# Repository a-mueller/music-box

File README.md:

# Music Box

A rfid based player I made. It basically scans for RFID takes, and looks for a WAV file on the SD card with that ID, if found it plays it.
The WAV files need to be 22khz, 16bit mono. Audacity is a good tool to convert mp3s.

## Board

The board is simply a pico with and SD card and the I2S chip.

See KiCad files.

### Schematic

### PCB

### BOM

<table>
<tr><td>CR1</td><td>PMEG2005AEA</td><td>https://uk.farnell.com/nexperia/pmeg2005aea-115/diode-schottky-sod-323/dp/8737843?st=pmeg2005aea</td></tr>
<tr><td>J2</td><td>GCT MEM2061-01-188-00-A</td><td>https://uk.farnell.com/gct-global-connector-technology/mem2061-01-188-00-a/micro-sd-conn-push-push-8pos-smt/dp/2678544?ost=mem2061-01-188-00-a</td></tr>
<tr><td>C6, C2</td><td>0.1uf, 0603</td><td></td></tr>
<tr><td>C5, C1</td><td>10uf, 0805</td><td></td></tr>
<tr><td>R2</td><td>Array, 4x 47k (EXB-N8V473JX)</td><td>https://uk.farnell.com/panasonic/exbn8v473jx/resistor-ccav-array-0402x4-47k/dp/2060146?st=EXBN8V473JX</td></tr>
<tr><td>R6</td><td>649k, 0402</td><td></td></tr>
<tr><td>U1</td><td>I2S Amp, MAX98357AETE+T</td><td>https://uk.farnell.com/analog-devices/max98357aete-t/audio-power-amp-d-40-to-85deg/dp/2949165?st=MAX98357AETE%20T</td></tr>
<tr><td>FB1, FB2</td><td>Ferrite Beads, MMZ1608B121CTDH5</td><td>https://uk.farnell.com/tdk/mmz1608b121ctdh5/ferrite-chip-bead-1608-0-15-ohm/dp/3386884?st=mmz1608b121ctdh5</td></tr>
<tr><td>C4,C3</td><td>220pf, 0402</td><td></td></tr>
<tr><td>J1</td><td>JST, XH 2.5mm</td><td></td></tr>
<tr><td>J4, J3, J5</td><td>JST, PH, 2mm</td><td></td></tr>

</table>

## Software

Flash circuit python (originally I used v9) and copy the lib folder and `code.py` files over. That should be it.

## Case

See FreeCad files in `3dPrinting`, you will need a usbc power board as well to power it (see https://github.com/a-mueller/usbc_power_supply_2)

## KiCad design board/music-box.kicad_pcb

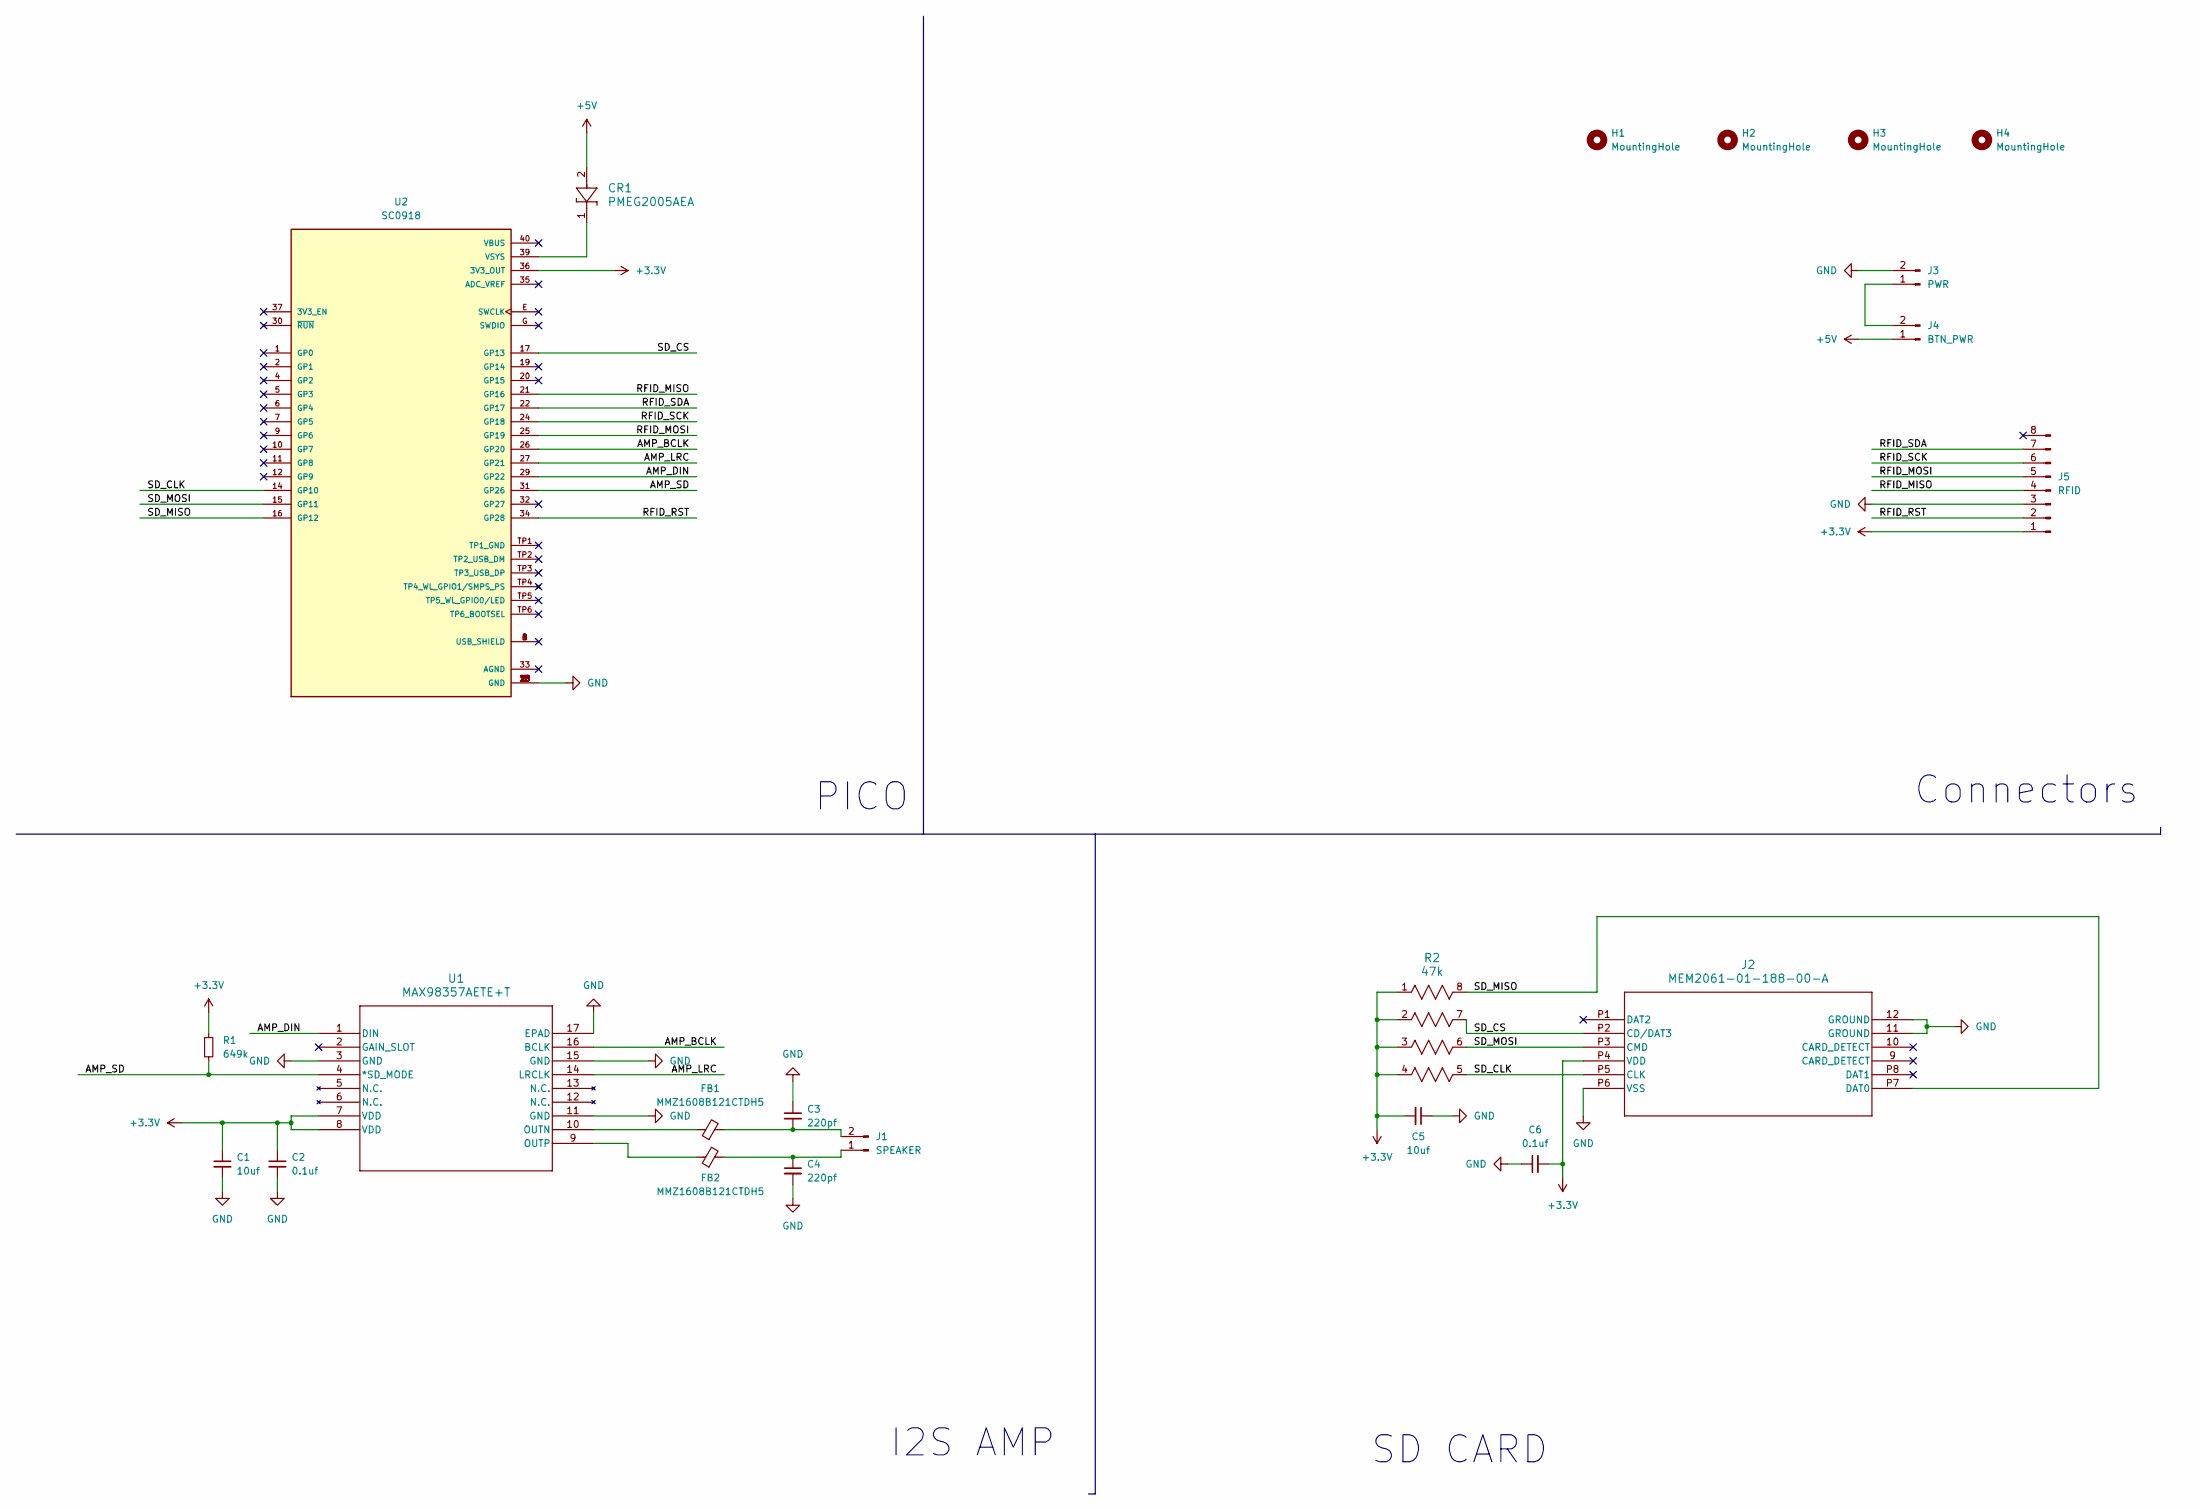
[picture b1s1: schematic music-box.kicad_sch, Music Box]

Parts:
C1, C5: 10uf; C_0805_2012Metric
C2, C6: 0.1uf; C_0603_1608Metric
C3, C4: 220pf; C_0402_1005Metric
CR1: PMEG2005AEA; SOD323F_NEX
FB1, FB2: MMZ1608B121CTDH5; L_0603_1608Metric
H1, H2, H3, H4: MountingHole; MountingHole_2.2mm_M2_DIN965
J1: SPEAKER; JST_XH_B2B-XH-A_1x02_P2.50mm_Vertical
J2: MEM2061-01-188-00-A; MEM2061-01-188-00-A_GCT
J3: PWR; JST_PH_B2B-PH-K_1x02_P2.00mm_Vertical
J4: BTN_PWR; JST_PH_B2B-PH-K_1x02_P2.00mm_Vertical
J5: RFID; JST_PH_B8B-PH-K_1x08_P2.00mm_Vertical
R1: 649k; R_0402_1005Metric
R2: 47k; EXBN8V_PAN
U1: MAX98357AETE+T; 21-0136I_T1633-4_MXM
U2: SC0918; MODULE_SC0918; PARTREV 2.1

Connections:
+3.3V: C1.1, C2.1, C5.2, C6.2, J2.P4 (VDD), J5.1, R1.1, R2.1, R2.2, R2.3, R2.4, U1.7 (VDD), U1.8 (VDD), U2.36 (3V3_OUT)
+5V: CR1.2, J4.1
/AMP_BCLK: U1.16 (BCLK), U2.26 (GP20)
/AMP_DIN: U1.1 (DIN), U2.29 (GP22)
/AMP_LRC: U1.14 (LRCLK), U2.27 (GP21)
/AMP_SD: R1.2, U1.4 (*SD_MODE), U2.31 (GP26)
/RFID_MISO: J5.4, U2.21 (GP16)
/RFID_MOSI: J5.5, U2.25 (GP19)
/RFID_RST: J5.2, U2.34 (GP28)
/RFID_SCK: J5.6, U2.24 (GP18)
/RFID_SDA: J5.7, U2.22 (GP17)
/SD_CLK: J2.P5 (CLK), R2.5, U2.14 (GP10)
/SD_CS: J2.P2 (CD/DAT3), R2.7, U2.17 (GP13)
/SD_MISO: J2.P7 (DAT0), R2.8, U2.16 (GP12)
/SD_MOSI: J2.P3 (CMD), R2.6, U2.15 (GP11)
GND: C1.2, C2.2, C3.1, C4.2, C5.1, C6.1, J2.11 (GROUND), J2.12 (GROUND), J2.P6 (VSS), J3.2, J5.3, U1.3 (GND), U1.11 (GND), U1.15 (GND), U1.17 (EPAD), U2.3 (GND), U2.8 (GND), U2.13 (GND), U2.18 (GND), U2.23 (GND), U2.28 (GND), U2.38 (GND), U2.F (GND)
unnamed: C4.1, FB2.2, J1.1
unnamed: C3.2, FB1.2, J1.2
unnamed: J3.1, J4.2
unnamed: FB1.1, U1.10 (OUTN)
unnamed: FB2.1, U1.9 (OUTP)
unnamed: CR1.1, U2.39 (VSYS)

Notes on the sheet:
Connectors
I2S AMP
PICO
SD CARD

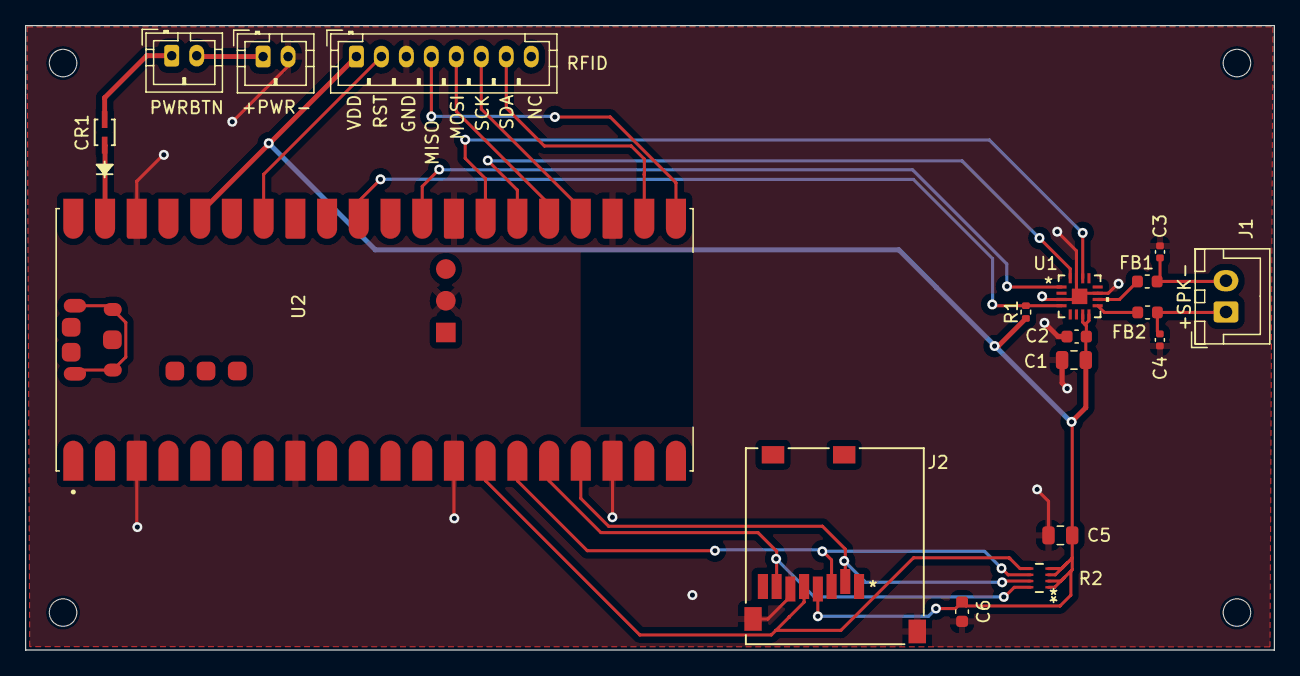
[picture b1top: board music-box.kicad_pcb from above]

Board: 2 copper layers, 100.0 x 50.0 mm, 22 parts (0 on the bottom side), 22 nets.

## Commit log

2024-04-02 adds board (KiCad)
2024-04-02 adds 3dPrinting files and test code
2024-04-02 adds readme * license
2024-04-10 fixed issue with board (rx / tx swap for the sd card)
2024-04-19 Updated docs
2024-04-19 fixed typo
2024-04-19 updates docs
2024-04-23 upgrades board files to kicad 8
2024-05-15 adds test code
